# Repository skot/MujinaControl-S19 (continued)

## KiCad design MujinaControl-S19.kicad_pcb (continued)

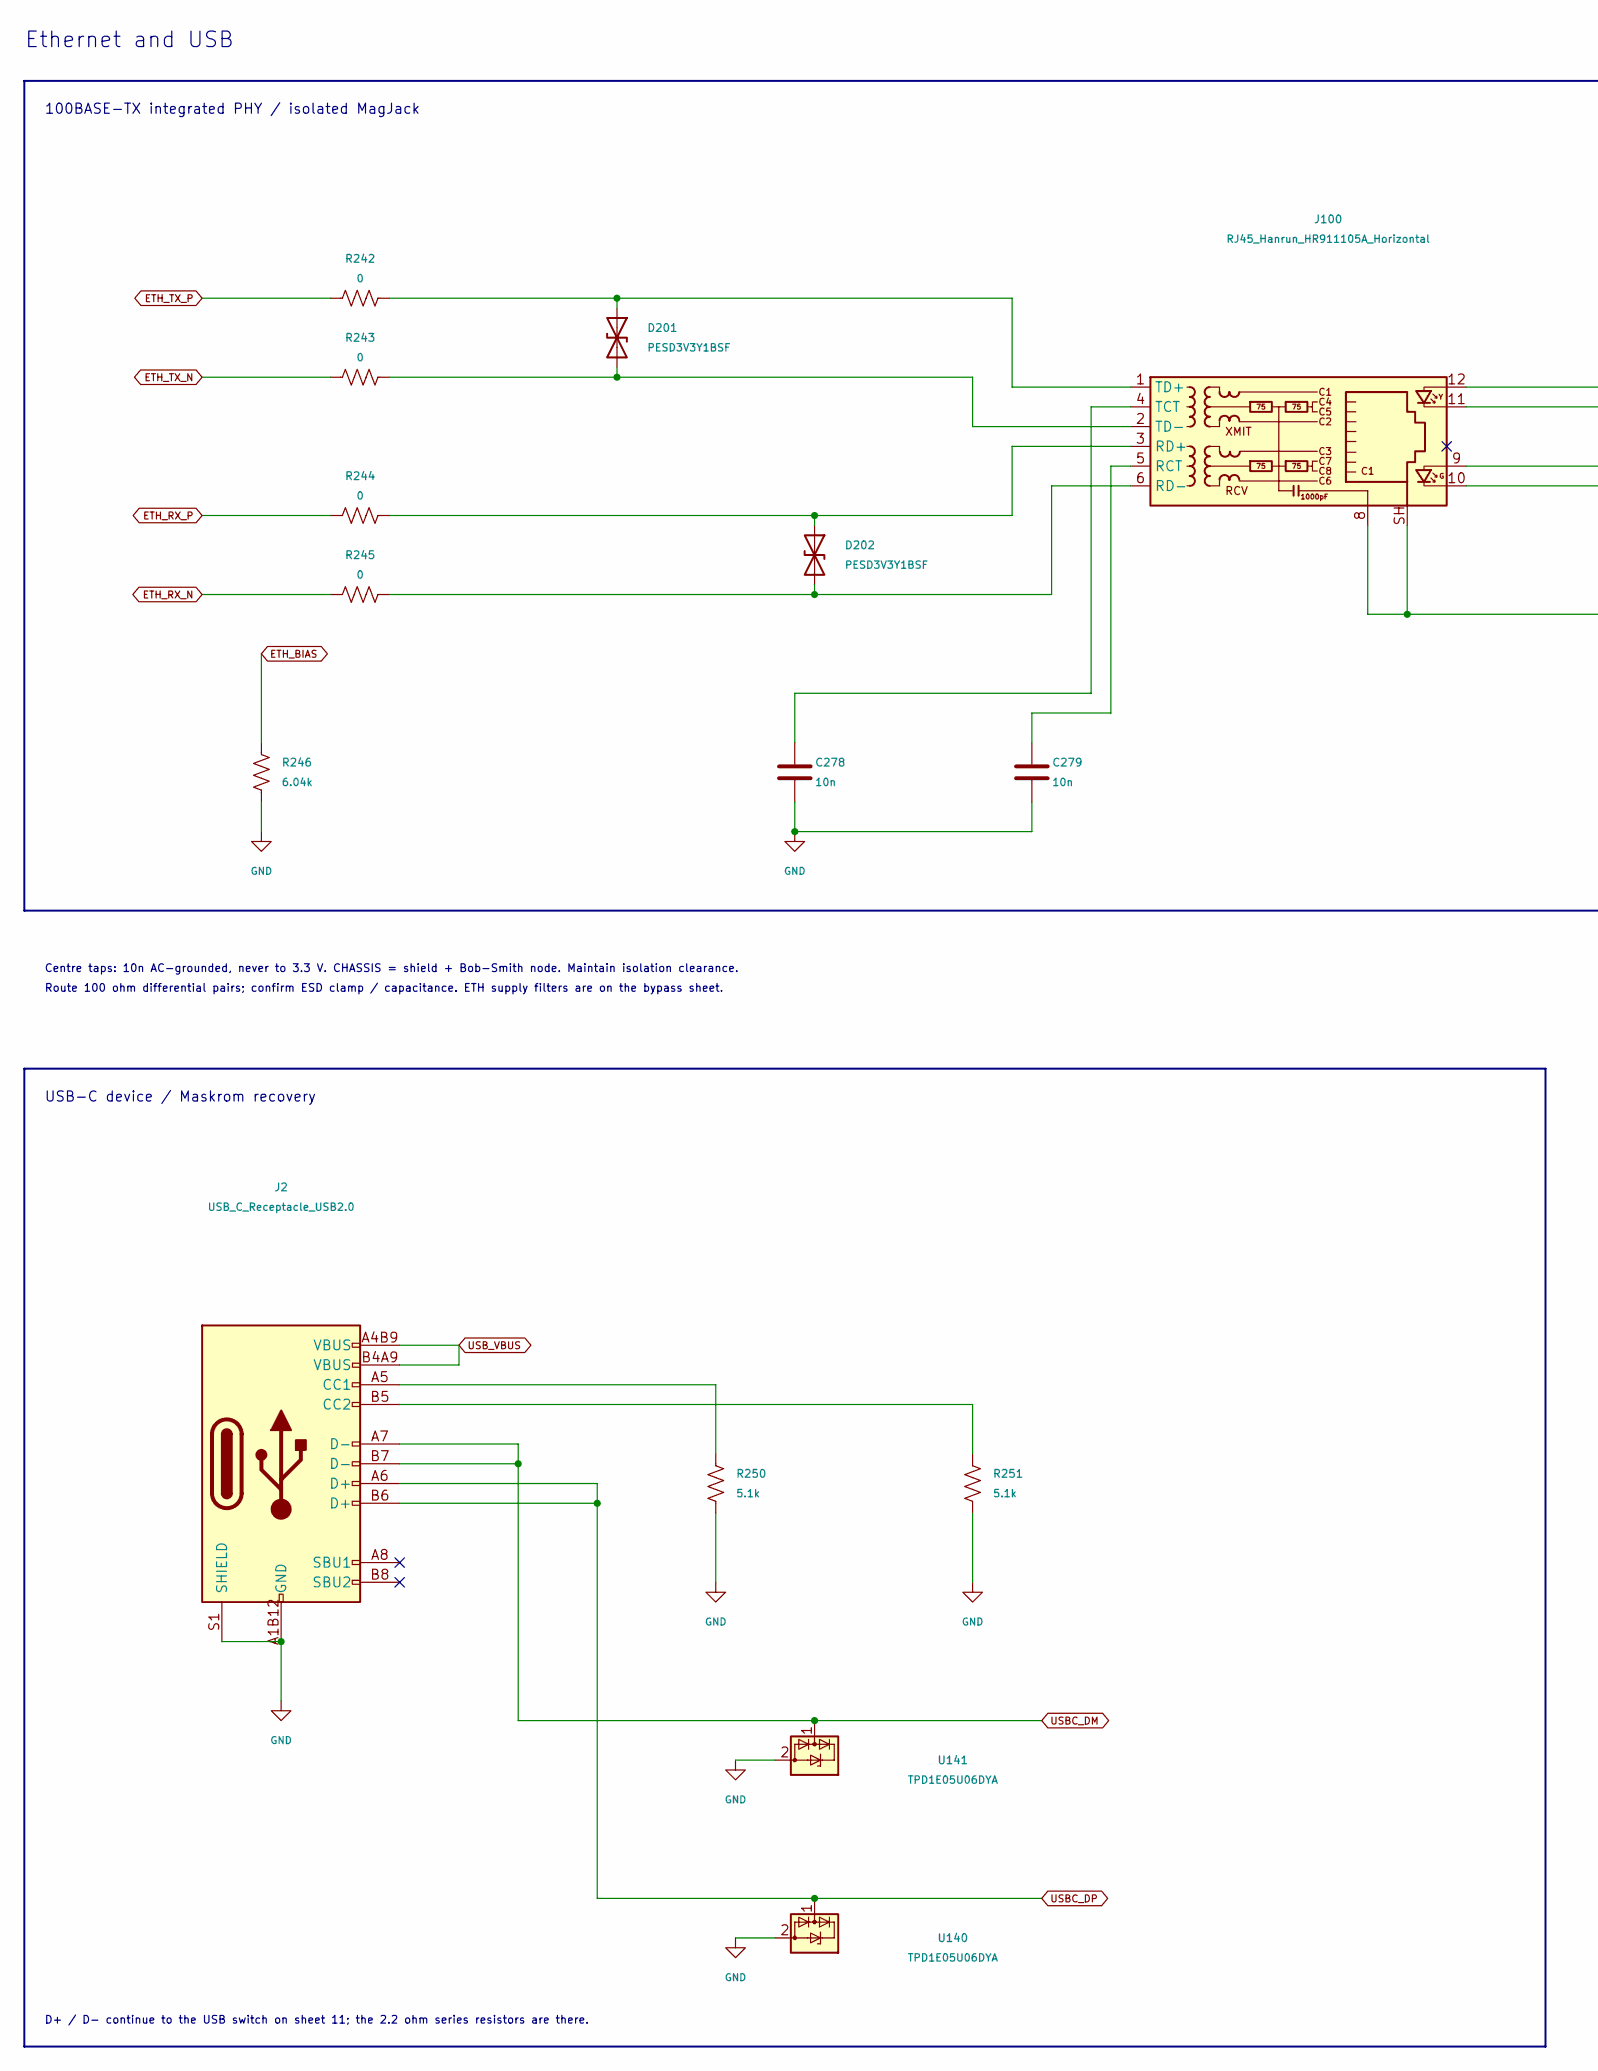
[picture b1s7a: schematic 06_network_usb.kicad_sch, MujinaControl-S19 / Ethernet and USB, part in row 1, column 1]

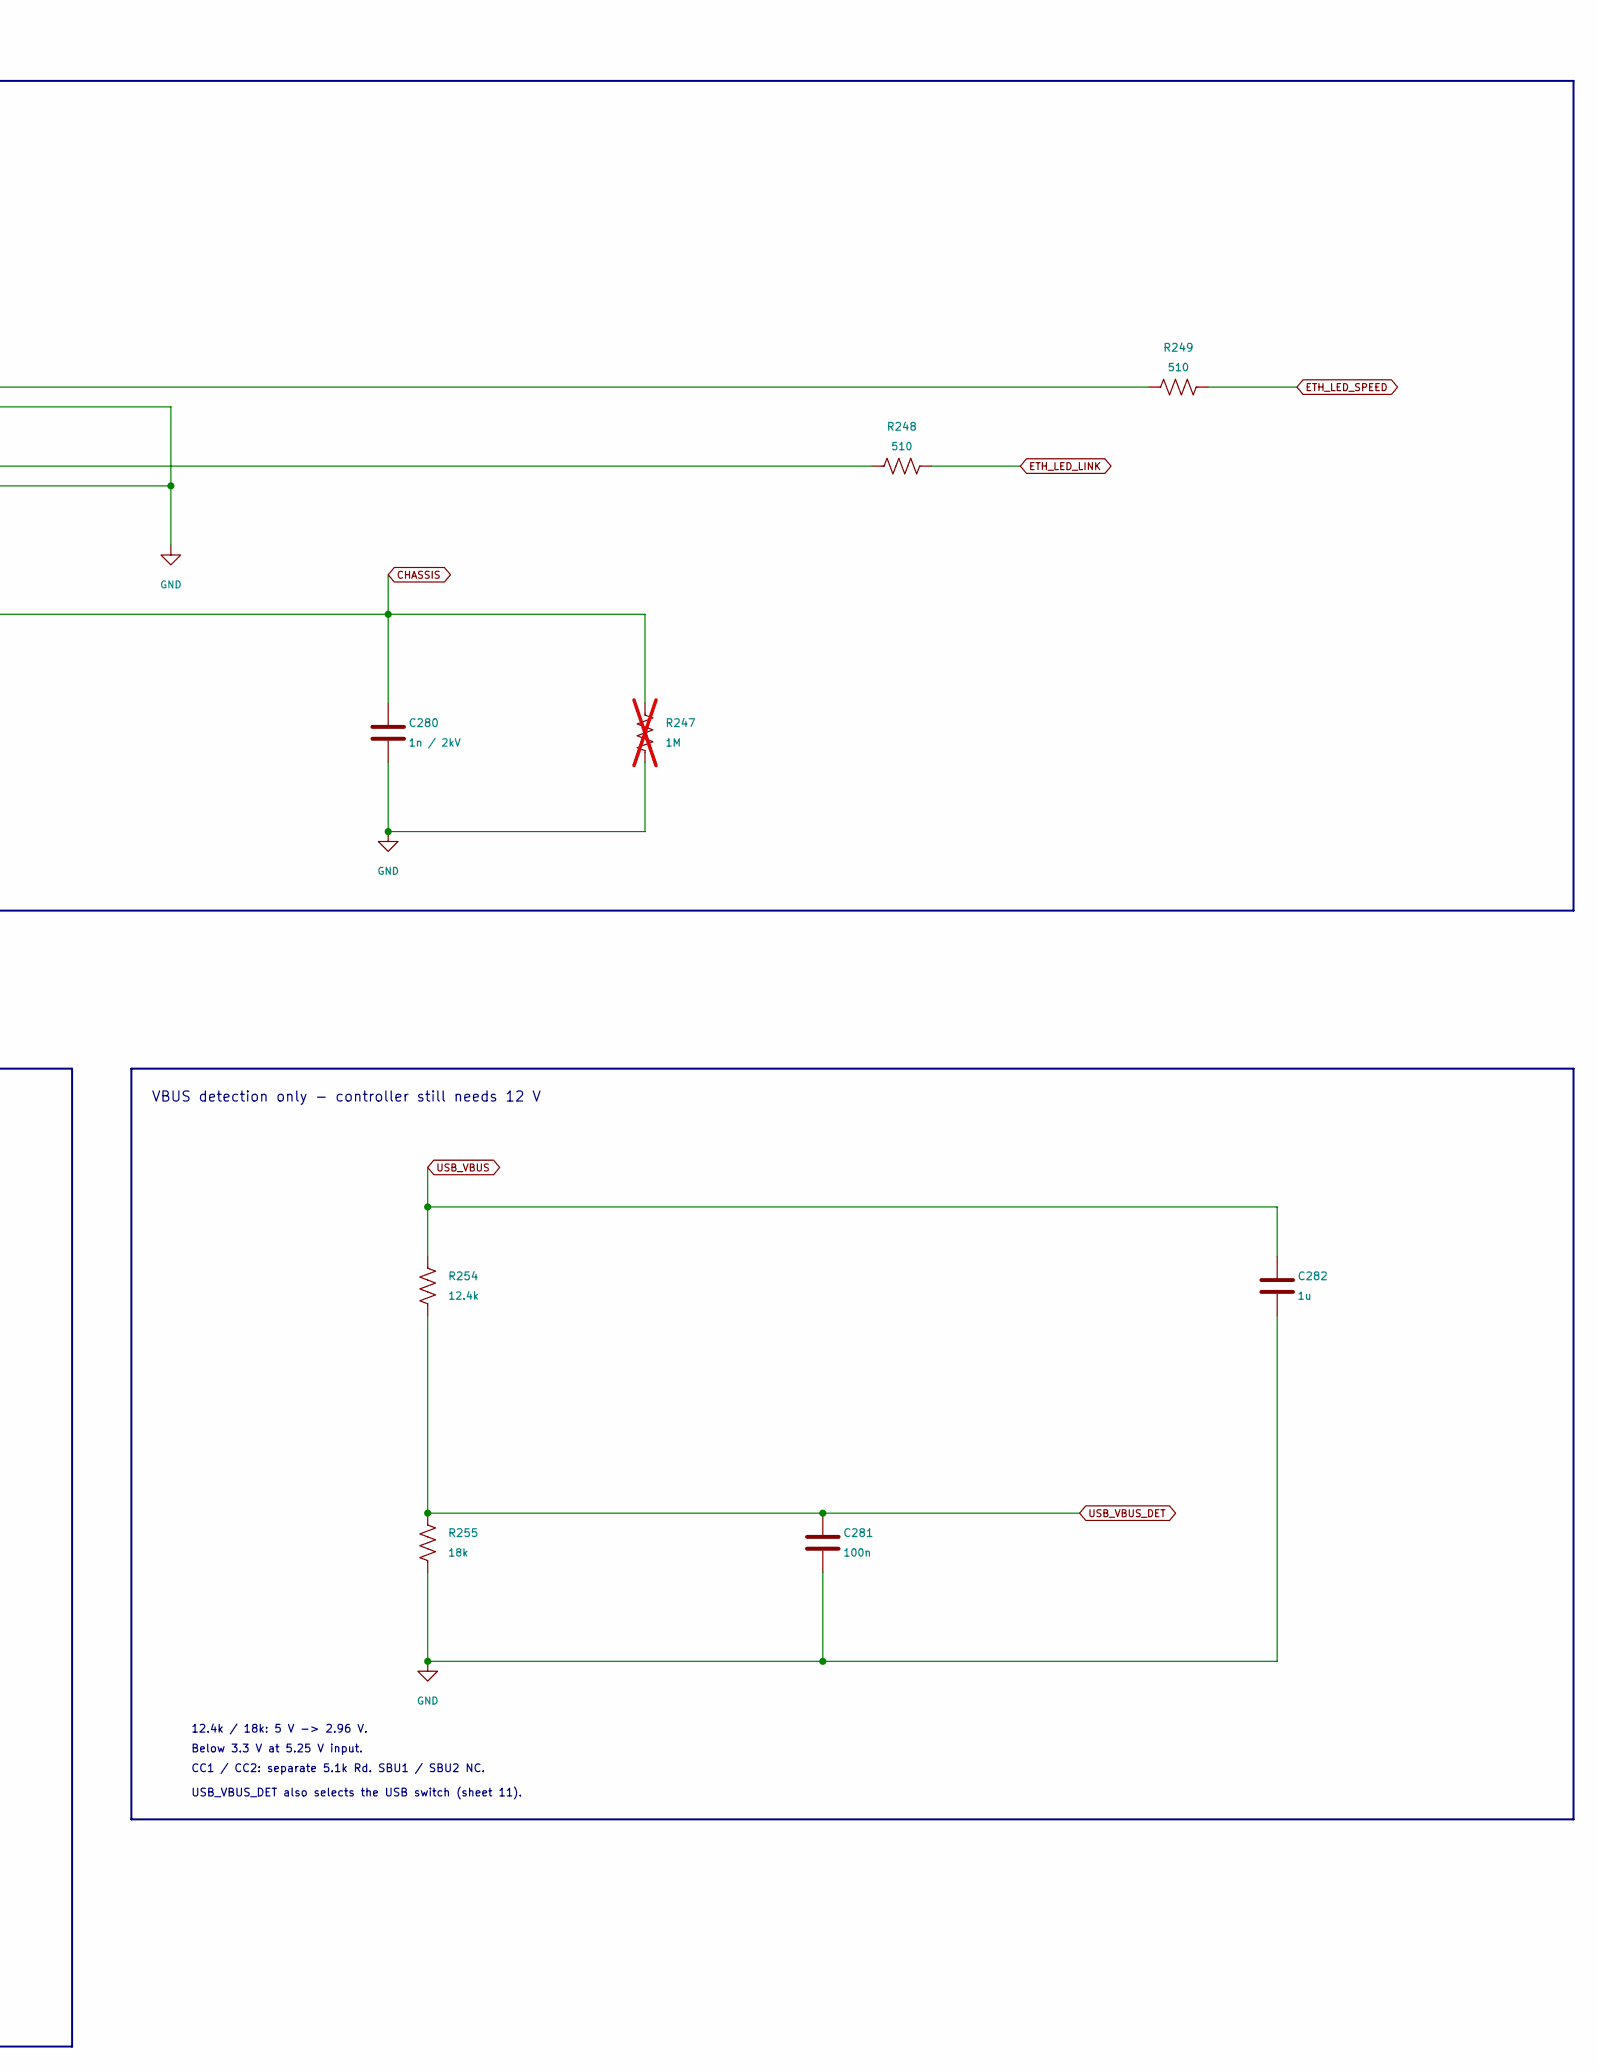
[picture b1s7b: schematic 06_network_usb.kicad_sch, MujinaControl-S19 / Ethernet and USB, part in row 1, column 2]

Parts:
C278, C279: 10n; C_0402_1005Metric; MPN CL05B103KB5NNNC; LCSC C15195
C280: 1n / 2kV; C_1808_4520Metric; MPN C1808C102KGRACTU; LCSC C2167485
C281: 100n; C_0402_1005Metric; MPN CL05B104KO5NNNC; LCSC C1525
C282: 1u; C_0402_1005Metric; MPN CL05A105KA5NQNC; LCSC C52923
D201, D202: PESD3V3Y1BSF; Nexperia_DSN0603-2_0.6x0.3mm_P0.4mm; MPN PESD3V3Y1BSFYL; LCSC C552535
J2: USB_C_Receptacle_USB2.0; USB_C_Receptacle_GCT_USB4105-xx-A_16P_TopMnt_Horizontal; MPN USB4105-GF-A; LCSC C3020560
J100: RJ45_Hanrun_HR911105A_Horizontal; MPN HR911105A; LCSC C12074
R242, R243, R244, R245: 0; R_0402_1005Metric; MPN 0402WGF0000TCE; LCSC C17168
R246: 6.04k; R_0402_1005Metric; MPN RC0402FR-076K04L; LCSC C97819
R247: 1M; R_0402_1005Metric; MPN 0402WGF1004TCE; LCSC C26083; not fitted
R248, R249: 510; R_0402_1005Metric; MPN 0402WGF5100TCE; LCSC C25123
R250, R251: 5.1k; R_0402_1005Metric; MPN 0402WGF5101TCE; LCSC C25905
R254: 12.4k; R_0402_1005Metric; MPN RC0402FR-0712K4L; LCSC C138060
R255: 18k; R_0402_1005Metric; MPN 0402WGF1802TCE; LCSC C25762
U140, U141: TPD1E05U06DYA; D_SOD-523; MPN TPD1E05U06DYA; LCSC C3702980

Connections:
CHASSIS: C280.1, J100.8, J100.SH, R247.1
ETH_BIAS: R246.1; also elsewhere on the board
ETH_LED_LINK: R248.1; also elsewhere on the board
ETH_LED_SPEED: R249.1; also elsewhere on the board
ETH_RX_N: R245.1; also elsewhere on the board
ETH_RX_P: R244.1; also elsewhere on the board
ETH_TX_N: R243.1; also elsewhere on the board
ETH_TX_P: R242.1; also elsewhere on the board
GND: C278.2, C279.2, C280.2, C281.2, C282.2, J2.A1B12 (GND), J2.B1A12 (GND), J2.S1 (SHIELD), J100.10, J100.11, R246.2, R247.2, R250.2, R251.2, R255.2, U140.2 (GND), U141.2 (GND); also elsewhere on the board
unnamed: D201.1 (A1), J100.1 (TD+), R242.2
unnamed: D201.2 (A2), J100.2 (TD-), R243.2
unnamed: D202.1 (A1), J100.3 (RD+), R244.2
unnamed: D202.2 (A2), J100.6 (RD-), R245.2
unnamed: J2.A5 (CC1), R250.1
unnamed: J2.B5 (CC2), R251.1
unnamed: J100.9, R248.2
unnamed: J100.12, R249.2
unnamed: C279.1, J100.5 (RCT)
unnamed: C278.1, J100.4 (TCT)
USBC_DM: J2.A7 (D-), J2.B7 (D-), U141.1 (I/O); also elsewhere on the board
USBC_DP: J2.A6 (D+), J2.B6 (D+), U140.1 (I/O); also elsewhere on the board
USB_VBUS: C282.1, J2.A4B9 (VBUS), J2.B4A9 (VBUS), R254.1
USB_VBUS_DET: C281.1, R254.2, R255.1; also elsewhere on the board

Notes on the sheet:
Ethernet and USB
100BASE-TX integrated PHY / isolated MagJack
USB_VBUS_DET also selects the USB switch (sheet 11).
12.4k / 18k: 5 V -> 2.96 V.
D+ / D- continue to the USB switch on sheet 11; the 2.2 ohm series resistors are there.
Centre taps: 10n AC-grounded, never to 3.3 V. CHASSIS = shield + Bob-Smith node. Maintain isolation clearance.
Route 100 ohm differential pairs; confirm ESD clamp / capacitance. ETH supply filters are on the bypass sheet.
Below 3.3 V at 5.25 V input.
CC1 / CC2: separate 5.1k Rd. SBU1 / SBU2 NC.
VBUS detection only - controller still needs 12 V
USB-C device / Maskrom recovery

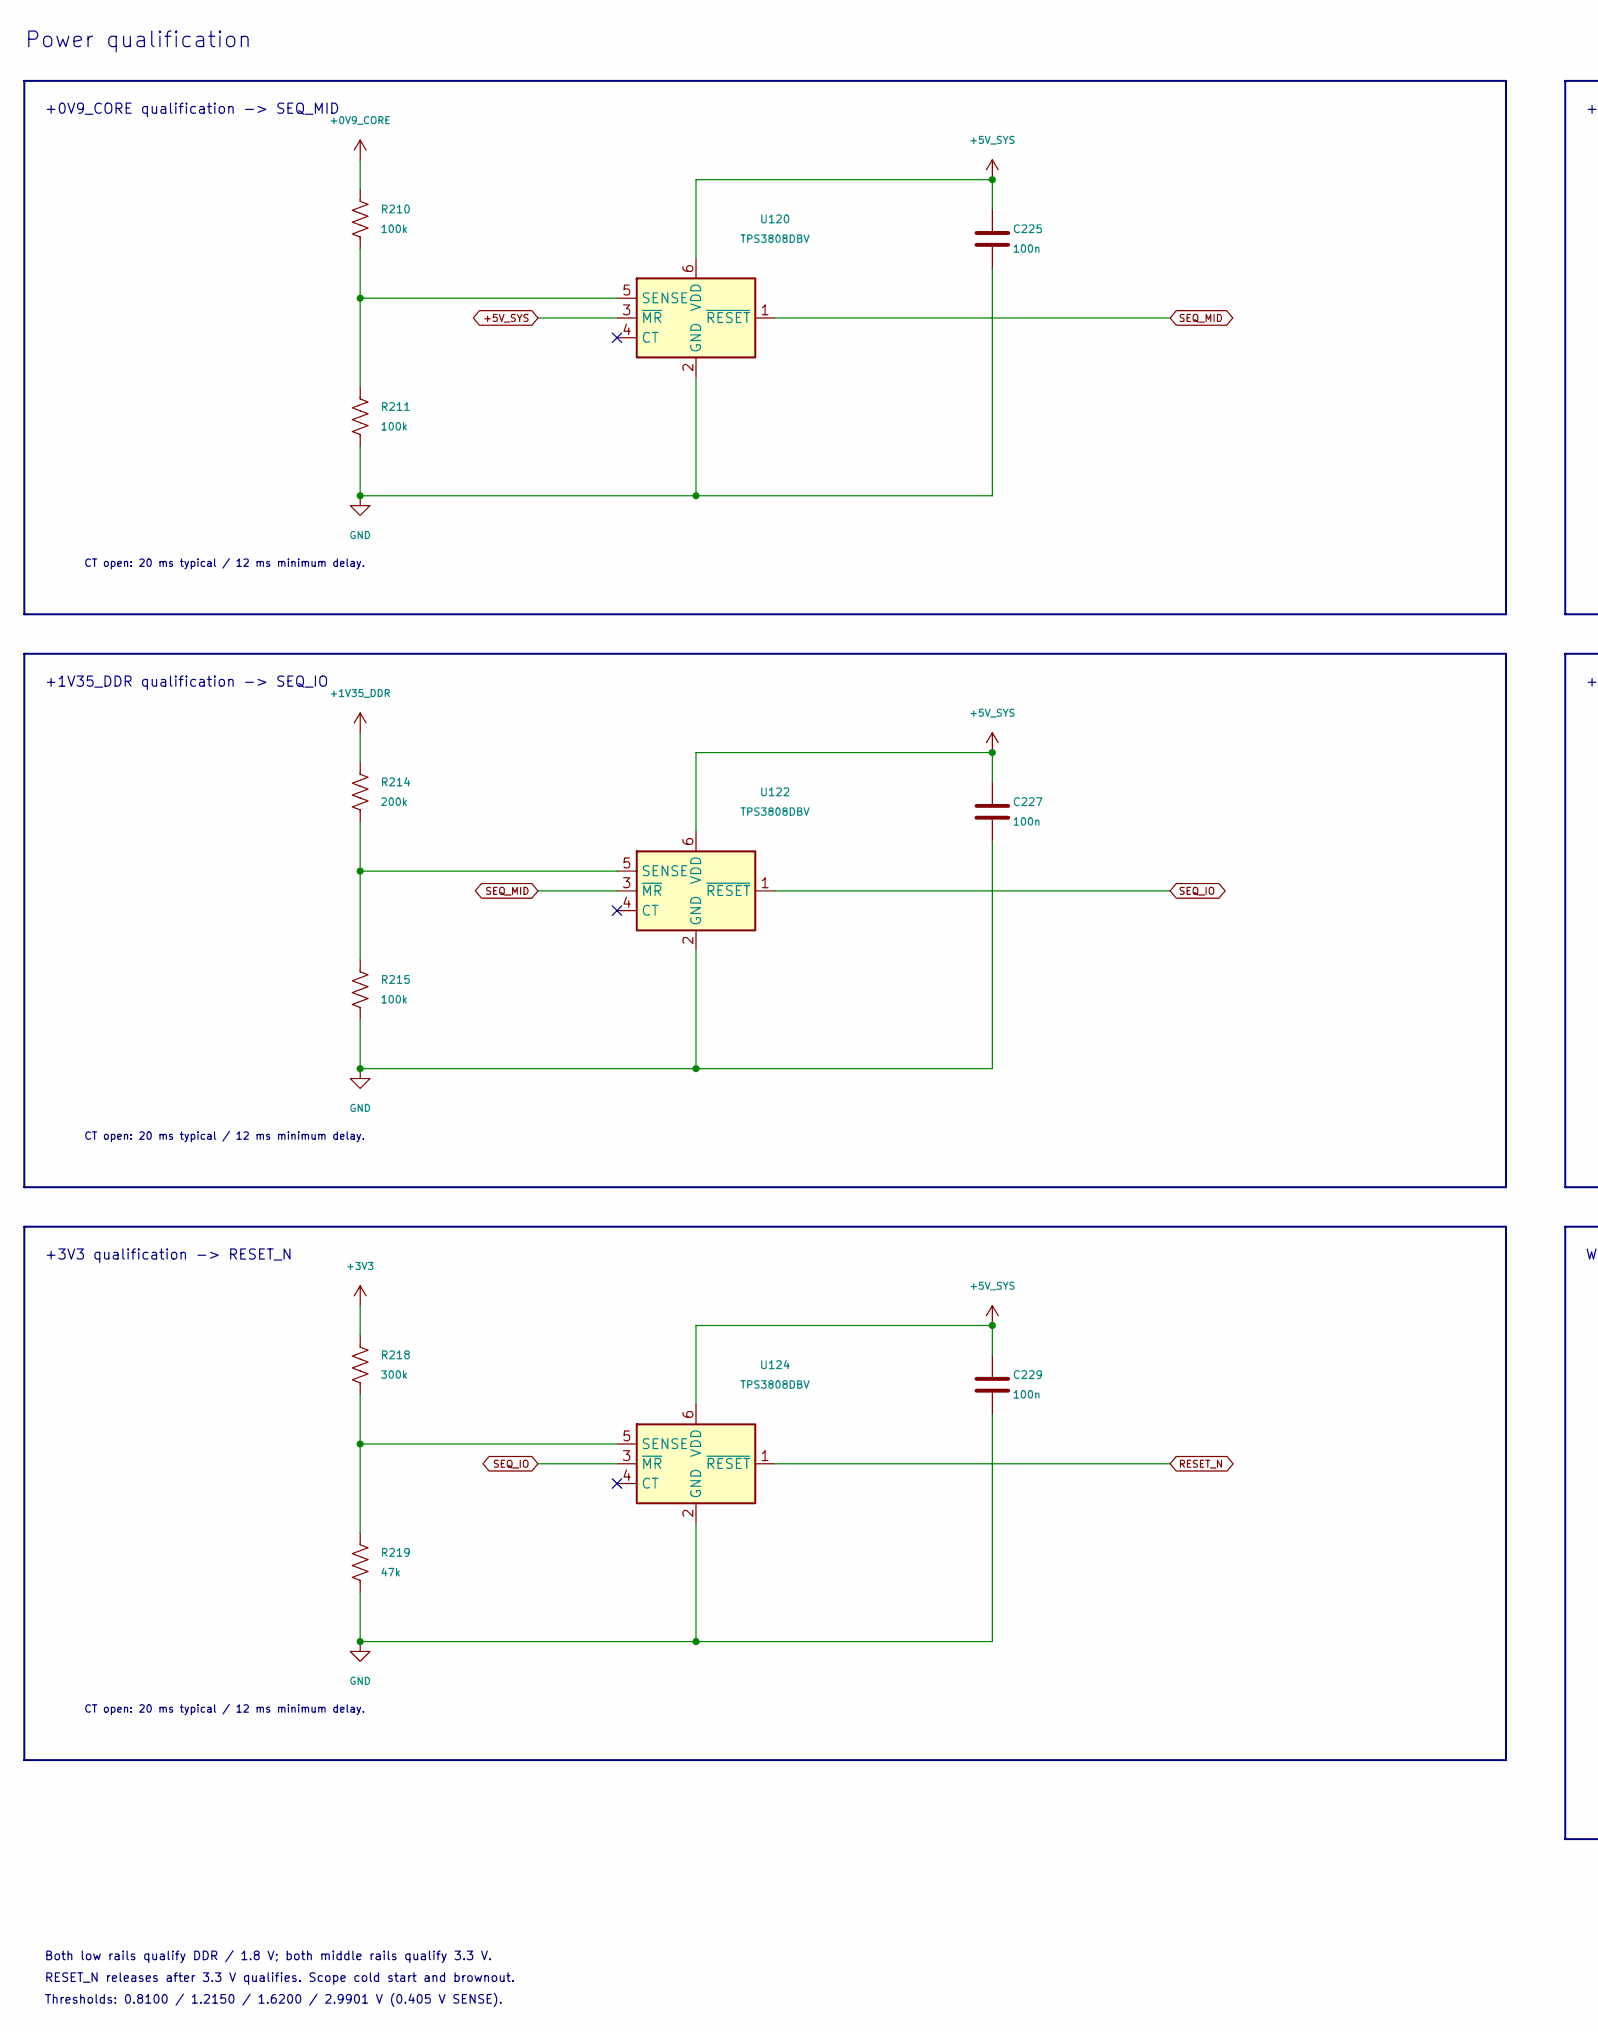
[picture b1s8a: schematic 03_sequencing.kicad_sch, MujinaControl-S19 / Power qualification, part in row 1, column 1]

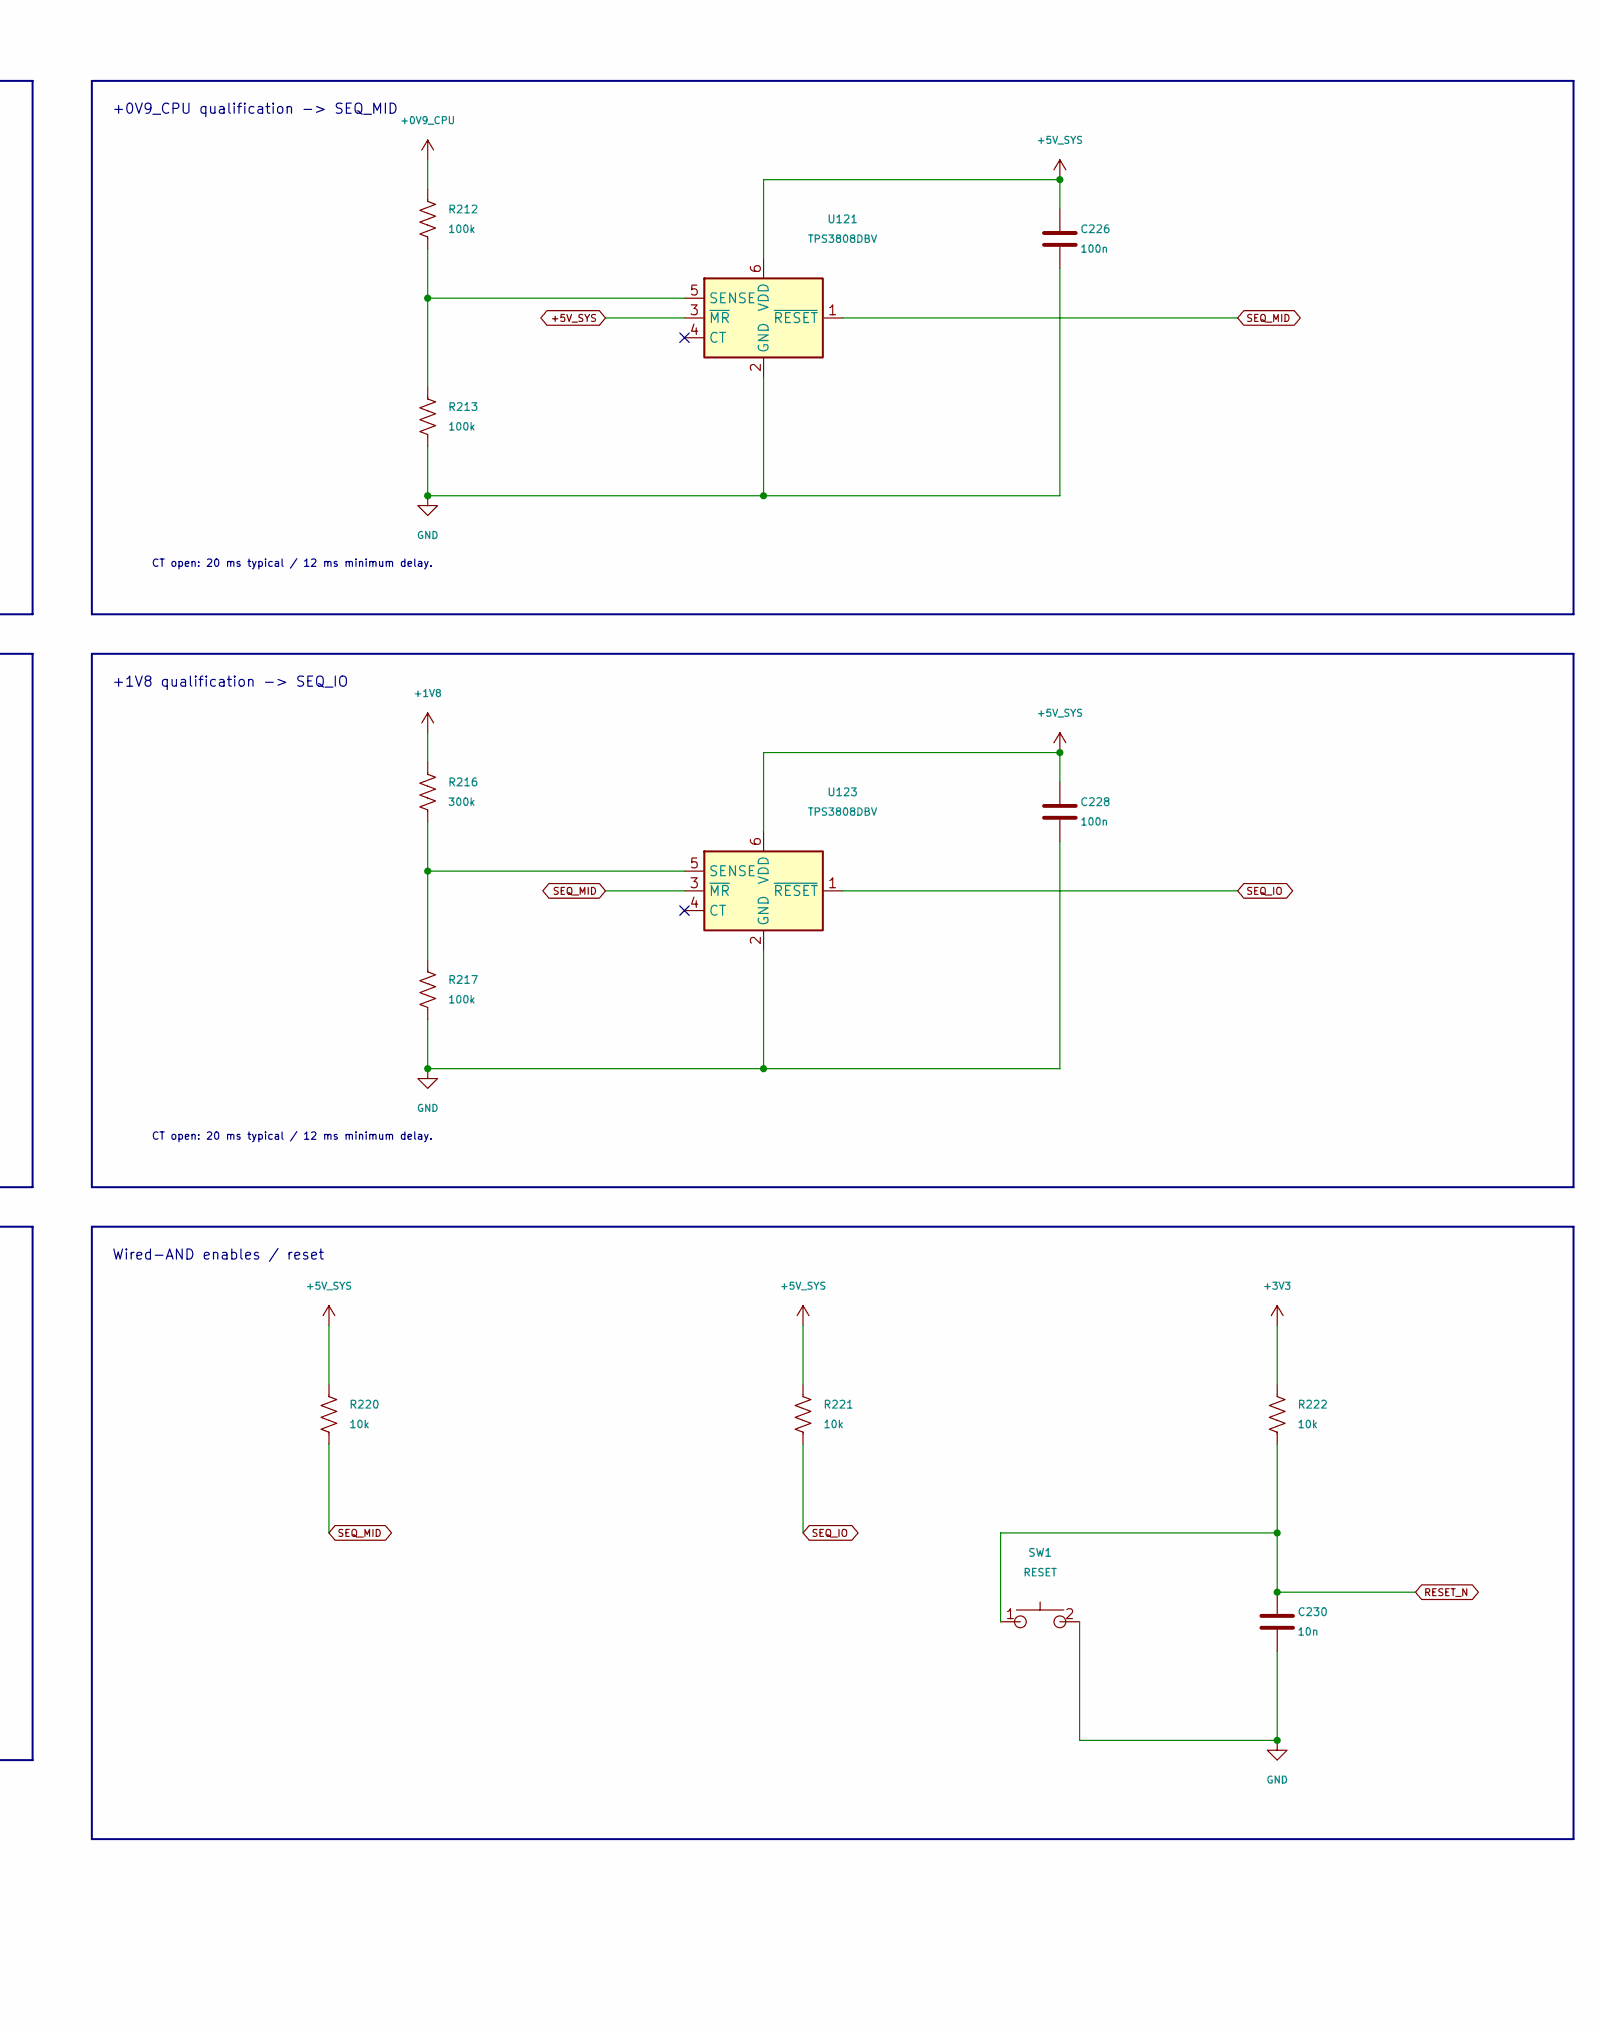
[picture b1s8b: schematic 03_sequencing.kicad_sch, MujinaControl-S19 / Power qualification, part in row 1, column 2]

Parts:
C225, C226, C227, C228, C229: 100n; C_0402_1005Metric; MPN CL05B104KO5NNNC; LCSC C1525
C230: 10n; C_0402_1005Metric; MPN CL05B103KB5NNNC; LCSC C15195
R210, R211, R212, R213, R215, R217: 100k; R_0402_1005Metric; MPN 0402WGF1003TCE; LCSC C25741
R214: 200k; R_0402_1005Metric; MPN 0402WGF2003TCE; LCSC C25764
R216, R218: 300k; R_0402_1005Metric; MPN 0402WGF3003TCE; LCSC C25774
R219: 47k; R_0402_1005Metric; MPN 0402WGF4702TCE; LCSC C25792
R220, R221, R222: 10k; R_0402_1005Metric; MPN 0402WGF1002TCE; LCSC C25744
SW1: RESET; SW-SMD_TC-S3601-3.5-260G-F0.6; MPN TC-S3601-3.5-260G-F0.6; LCSC C49101620
U120, U121, U122, U123, U124: TPS3808DBV; SOT-23-6; MPN TPS3808G01DBVR-TP; LCSC C42394092

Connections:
+0V9_CORE: R210.1; also elsewhere on the board
+0V9_CPU: R212.1; also elsewhere on the board
+1V8: R216.1; also elsewhere on the board
+1V35_DDR: R214.1; also elsewhere on the board
+3V3: R218.1, R222.1; also elsewhere on the board
+5V_SYS: C225.1, C226.1, C227.1, C228.1, C229.1, R220.1, R221.1, U120.3 (~MR), U120.6 (VDD), U121.3 (~MR), U121.6 (VDD), U122.6 (VDD), U123.6 (VDD), U124.6 (VDD); also elsewhere on the board
GND: C225.2, C226.2, C227.2, C228.2, C229.2, C230.2, R211.2, R213.2, R215.2, R217.2, R219.2, SW1.2, U120.2 (GND), U121.2 (GND), U122.2 (GND), U123.2 (GND), U124.2 (GND); also elsewhere on the board
unnamed: R210.2, R211.1, U120.5 (SENSE)
unnamed: R212.2, R213.1, U121.5 (SENSE)
unnamed: R214.2, R215.1, U122.5 (SENSE)
unnamed: R216.2, R217.1, U123.5 (SENSE)
unnamed: R218.2, R219.1, U124.5 (SENSE)
RESET_N: C230.1, R222.2, SW1.1, U124.1 (~RESET); also elsewhere on the board
SEQ_IO: R221.2, U122.1 (~RESET), U123.1 (~RESET), U124.3 (~MR); also elsewhere on the board
SEQ_MID: R220.2, U120.1 (~RESET), U121.1 (~RESET), U122.3 (~MR), U123.3 (~MR); also elsewhere on the board

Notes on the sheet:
Wired-AND enables / reset
+1V8 qualification -> SEQ_IO
+0V9_CPU qualification -> SEQ_MID
+1V35_DDR qualification -> SEQ_IO
Thresholds: 0.8100 / 1.2150 / 1.6200 / 2.9901 V (0.405 V SENSE).
+3V3 qualification -> RESET_N
+0V9_CORE qualification -> SEQ_MID
Both low rails qualify DDR / 1.8 V; both middle rails qualify 3.3 V.
RESET_N releases after 3.3 V qualifies. Scope cold start and brownout.
Power qualification
CT open: 20 ms typical / 12 ms minimum delay.

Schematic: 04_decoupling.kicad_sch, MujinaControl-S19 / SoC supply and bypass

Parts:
C231, C232, C233, C234, C235, C236, C237, C238, C239, C241, C243, C244, C245, C247, C248, C249, C250, C251, C252, C253, C255, C256, C257, C258, C262, C263, C265: 100n; C_0402_1005Metric; MPN CL05B104KO5NNNC; LCSC C1525
C240, C242, C246, C254, C259, C260: 10u; C_0805_2012Metric; MPN CL21A106KAYNNNE; LCSC C15850
C261, C264, C266, C267: 1u; C_0402_1005Metric; MPN CL05A105KA5NQNC; LCSC C52923
FB201, FB202: 120R @ 100MHz; L_0402_1005Metric; MPN BLM15AG121SN1D; LCSC C85812
H1, H2, H3, H4: MountingHole_Pad; MountingHole_3mm_Pad; MPN PCB_MOUNTING_HOLE; LCSC N/A
R223: 1; R_0402_1005Metric; MPN 0402WGF100KTCE; LCSC C25086
R224: 100; R_0402_1005Metric; MPN 0402WGF1000TCE; LCSC C25076
U100: RV1106G2; Rockchip_QFN-128-1EP_12.3x12.3mm_P0.35mm_EP7x7mm; MPN RV1106G2; LCSC C5272606

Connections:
+0V9_CORE: C231.1, C232.1, C233.1, C234.1, C235.1, C236.1, C237.1, C238.1, C239.1, C240.1, C260.1, U100.10 (DVDD_1), U100.51 (DVDD_2), U100.54 (DVDD_3), U100.55 (DVDD_4), U100.67 (PMU_DVDD0V9), U100.71 (OSC_PLL_DVDD), U100.82 (DVDD_5), U100.103 (DVDD_6), U100.116 (DVDD_7); also elsewhere on the board
+0V9_CPU: C241.1, C242.1, C261.1, U100.115 (CPU_DVDD); also elsewhere on the board
+1V8: C255.1, C256.1, C257.1, C258.1, C259.1, FB201.1, R223.1, U100.1 (MIPI_AVDD1V8), U100.31 (CODEC_AVDD1V8), U100.53 (DDR_PLL_AVDD1V8), U100.70 (OSC_AVDD1V8); also elsewhere on the board
+1V35_DDR: C243.1, C244.1, C245.1, C246.1, U100.49 (DDR_VDDQ_1), U100.50 (DDR_VDDQ_2), U100.56 (DDR_VDDQ_3); also elsewhere on the board
+3V3: C247.1, C248.1, C249.1, C250.1, C251.1, C252.1, C253.1, C254.1, FB202.1, R224.1, U100.13 (GPIO4_VCC), U100.28 (USB_AVDD3V3), U100.43 (GPIO3_VCC), U100.61 (PMU_VCC3V3), U100.81 (GPIO1_VCC3V3), U100.88 (GPIO6_VCC), U100.108 (GPIO5_VCC); also elsewhere on the board
ETH_1V8: C263.1, C264.1, FB201.2, U100.96 (OTP_AVDD1V8)
ETH_3V3: C265.1, C266.1, FB202.2, U100.101 (ETH_AVDD3V3)
GND: C231.2, C232.2, C233.2, C234.2, C235.2, C236.2, C237.2, C238.2, C239.2, C240.2, C241.2, C242.2, C243.2, C244.2, C245.2, C246.2, C247.2, C248.2, C249.2, C250.2, C251.2, C252.2, C253.2, C254.2, C255.2, C256.2, C257.2, C258.2, C259.2, C260.2, C261.2, C262.2, C263.2, C264.2, C265.2, C266.2, C267.2, H1.1 (1_1), H2.1 (1_1), H3.1 (1_1), H4.1 (1_1), U100.37 (GND), U100.57 (GND), U100.129 (GND_EP); also elsewhere on the board
RTC_3V3: C267.1, R224.2, U100.19 (RTC_AVDD3V3)
USB_1V8: C262.1, R223.2, U100.24 (SARADC_USB_AVDD1V8)

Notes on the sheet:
DDR3L: 1.35 V
CPU supply
Place each ceramic at its supply pin. Tie all ground pins and EP129
SoC supply and bypass
1.8 V analog / I/O
ETH_1V8 also supplies OTP / TSADC; place bead at pin 96.
to solid ground planes. RTC 100R / 1u is required by Rockchip.
U100 power distribution / exposed pad
Bulk / filtered analog rails
Core: one 100n per supply pin
Chassis mounting pads
3.3 V I/O

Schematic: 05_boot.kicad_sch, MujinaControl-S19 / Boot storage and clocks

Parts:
C268, C271: 100n; C_0402_1005Metric; MPN CL05B104KO5NNNC; LCSC C1525
C269, C277: 1u; C_0402_1005Metric; MPN CL05A105KA5NQNC; LCSC C52923
C270: 10u; C_0805_2012Metric; MPN CL21A106KAYNNNE; LCSC C15850
C272, C273, C274, C275: 18p; C_0402_1005Metric; MPN 0402CG180J500NT; LCSC C1549
C276: 1n; C_0402_1005Metric; MPN 0402B102K500NT; LCSC C1523
J16: UART2 DEBUG; PinHeader_1x03_P2.54mm_Vertical; MPN 61300311121; LCSC C2915006
J18: JTAG; PinHeader_1x05_P2.54mm_Vertical; MPN 61300511121; LCSC C6461551; not fitted
J101: Micro_SD_Card_Det2; microSD_HC_Hirose_DM3D-SF; MPN DM3D-SF; LCSC C719027
R225, R235, R236: 22; R_0402_1005Metric; MPN 0402WGF220JTCE; LCSC C25092
R226, R227, R228, R229, R230, R231, R232, R233, R234, R238, R240: 10k; R_0402_1005Metric; MPN 0402WGF1002TCE; LCSC C25744
R237: 1M; R_0402_1005Metric; MPN 0402WGF1004TCE; LCSC C26083; not fitted
R239: 100; R_0402_1005Metric; MPN 0402WGF1000TCE; LCSC C25076
R241: 240; R_0402_1005Metric; MPN RC0402FR-07240RL; LCSC C114755
SW2: BOOT; SW-SMD_TC-S3601-3.5-260G-F0.6; MPN TC-S3601-3.5-260G-F0.6; LCSC C49101620
U130: W25N02KVZEIR; WSON-8-1EP_8x6mm_P1.27mm_EP3.4x4.3mm; MPN W25N02KVZEIR; LCSC C3010298
Y100: 24MHz / CL12pF; Crystal_SMD_3225-4Pin_3.2x2.5mm; MPN X322524MOB4SI; LCSC C70590
Y101: 32.768kHz / CL12.5pF; Crystal_SMD_3215-2Pin_3.2x1.5mm; MPN Q13FC13500004; LCSC C32346

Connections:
+1V8: R238.1; also elsewhere on the board
+3V3: C268.1, C269.1, C270.1, C271.1, J18.1, J101.4 (VDD), R226.1, R227.1, R228.1, R229.1, R230.1, R231.1, R232.1, R233.1, R234.1, R240.1, U130.8 (VCC); also elsewhere on the board
BOOT_ADC: C276.1, R238.2, R239.1; also elsewhere on the board
CODEC_VCM: C277.1; also elsewhere on the board
DEBUG_RX: J16.3, R240.2; also elsewhere on the board
DEBUG_TX: J16.1; also elsewhere on the board
DRAM_ZQ: R241.1; also elsewhere on the board
FSPI_CLK: R225.2, U130.6 (SCLK)
FSPI_CLK_SOC: R225.1; also elsewhere on the board
FSPI_CS_N: R226.2, U130.1 (~CS); also elsewhere on the board
FSPI_D0: U130.5 (SI/IO0); also elsewhere on the board
FSPI_D1: U130.2 (SO/IO1); also elsewhere on the board
FSPI_D2: R227.2, U130.3 (~WP/IO2); also elsewhere on the board
FSPI_D3: R228.2, U130.7 (~HOLD/~RESET/IO3); also elsewhere on the board
GND: C268.2, C269.2, C270.2, C271.2, C272.2, C273.2, C274.2, C275.2, C276.2, C277.2, J16.2, J18.5, J101.6 (VSS), J101.10 (DET_A), J101.SH (SHIELD), R241.2, SW2.2, U130.4 (VSS), U130.9 (PAD), Y100.2 (G), Y100.4 (G); also elsewhere on the board
unnamed: C272.1, R236.2, Y100.1
unnamed: R239.2, SW2.1
OSC_XIN: C273.1, R237.2, Y100.3; also elsewhere on the board
OSC_XOUT: R236.1, R237.1; also elsewhere on the board
RESET_N: J18.4; also elsewhere on the board
RTC_XIN: C274.1, Y101.1; also elsewhere on the board
RTC_XOUT: C275.1, Y101.2; also elsewhere on the board
SD_CLK: J101.5 (CLK), R235.2
SD_CLK_SOC: R235.1; also elsewhere on the board
SD_CMD: J101.3 (CMD), R229.2; also elsewhere on the board
SD_D0: J101.7 (DAT0), R230.2; also elsewhere on the board
SD_D1: J101.8 (DAT1), R231.2; also elsewhere on the board
SD_D2: J18.3, J101.1 (DAT2), R232.2; also elsewhere on the board
SD_D3: J18.2, J101.2 (DAT3/CD), R233.2; also elsewhere on the board
SD_DET_N: J101.9 (DET_B), R234.2; also elsewhere on the board

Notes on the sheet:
18p crystal loads assume ~3p parasitic: measure startup and frequency.
Main oscillator / RTC crystal
Boot storage and clocks
BOOT key / UART debug / JTAG header / bias
J16: 1 = SoC TX; 2 = GND; 3 = SoC RX. 3.3 V only.
microSD - development / alternate boot
J18 (not fitted): 1 = 3.3 V reference; 2 = TMS (SD_D3); 3 = TCK (SD_D2); 4 = RESET_N; 5 = GND.
256 MB SPI NAND - normal boot
JTAG is an alternate function of the SD_D2 / SD_D3 pins (JTAG_CPU_TCK_M0 / TMS_M0): use it with no microSD card inserted.
SPI NAND has priority over SD. Hold BOOT during reset for USB recovery.
CPU JTAG, 2-wire - not fitted

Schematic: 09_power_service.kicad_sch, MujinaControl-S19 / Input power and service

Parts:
C283, C303, C304, C305: 100n; C_0402_1005Metric; MPN CL05B104KO5NNNC; LCSC C1525
C284, C285: 10u / 50V; C_1210_3225Metric; MPN CL32B106KBJNNNE; LCSC C138687
C286, C302: 100n / 50V; C_0402_1005Metric; MPN CL05B104KB54PNC; LCSC C307331
C287, C288: 22u / 25V; C_0805_2012Metric; MPN CL21A226MAQNNNE; LCSC C45783
C301: 33n / 50V; C_0603_1608Metric; MPN CL10B333KB8NNNC; LCSC C21117
D2: BZX84C12; SOT-23-3_L2.9-W1.6-P1.90-LS2.8-BR; MPN BZX84C12; LCSC C19077471
D220: SMBJ15A; D_SMB; MPN SMBJ15A; LCSC C19077569
J1: 0455580003; CONN-TH_50362462; MPN 50362462; LCSC C492365
J10: PSU Comm; CONN-TH_6P-P2.00_PHD-2X3A; MPN HC-PHD-2*3A; LCSC C2845614
J15: ACC 2x20 / 0.1 in; PinHeader_2x20_P2.54mm_Vertical; MPN PZ2.54-2*20; LCSC C5224014; not fitted
L210: 1.5u; IND-SMD_L2.0-W1.6; MPN FTC201612S1R5MBCA; LCSC C5832350
Q1: NTTFS008P03P8Z; onsemi_WDFN-8_3.3x3.3mm_P0.65mm_CASE483AW; MPN NTTFS008P03P8Z; LCSC C894097
R270, R279: 10k; R_0402_1005Metric; MPN 0402WGF1002TCE; LCSC C25744
R271: 100k; R_0402_1005Metric; MPN 0402WGF1003TCE; LCSC C25741
R272, R273: 4.7k; R_0402_1005Metric; MPN 0402WGF4701TCE; LCSC C25900; not fitted
R282, R284: 27k; R_0402_1005Metric; MPN 0402WGF2702TCE; LCSC C25771
R283, R285: 5.1k; R_0402_1005Metric; MPN 0402WGF5101TCE; LCSC C25905
R286, R287: 4.7k; R_0402_1005Metric; MPN 0402WGF4701TCE; LCSC C25900
TP29, TP30: TestPoint; TestPoint_Pad_D1.0mm; MPN PCB_TESTPOINT; LCSC N/A
U115: TPS62933DRLR; SOT-583-8_L2.1-W1.2-P0.50-LS1.6-BR; MPN TPS62933DRLR; LCSC C3200405

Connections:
+1V8: C305.1, J15.26; also elsewhere on the board
+3V3: C304.1, J15.3, J15.4, R272.1, R273.1, R286.1, R287.1; also elsewhere on the board
+5V_SYS: C287.1, C288.1, C303.1, J15.1, J15.2, L210.2, R282.1; also elsewhere on the board
+12V_FAN: C283.1, C284.1, C285.1, C302.1, D2.3 (K), D220.1 (K), Q1.1 (S), Q1.2 (S), Q1.3 (S), R284.1, U115.3 (VIN); also elsewhere on the board
+12V_IN: J1.1, J1.2, J1.3, Q1.5 (D), Q1.6 (D), Q1.7 (D), Q1.8 (D)
ACC1V8_GPIO3_C4: J15.27; also elsewhere on the board
ACC1V8_GPIO3_C5: J15.28; also elsewhere on the board
ACC1V8_GPIO3_C6: J15.29; also elsewhere on the board
ACC1V8_GPIO3_C7: J15.33; also elsewhere on the board
ACC1V8_GPIO3_D0: J15.34; also elsewhere on the board
ACC1V8_GPIO3_D1: J15.35; also elsewhere on the board
ACC1V8_GPIO3_D2: J15.36; also elsewhere on the board
ACC1V8_GPIO3_D3: J15.30; also elsewhere on the board
ACC_GPIO0_A0: J15.10; also elsewhere on the board
ACC_GPIO0_A1: J15.9; also elsewhere on the board
ACC_GPIO0_A2: J15.15; also elsewhere on the board
ACC_GPIO0_A4: J15.16; also elsewhere on the board
ACC_GPIO4_A5: J15.12; also elsewhere on the board
ACC_GPIO4_A7: J15.11; also elsewhere on the board
ACC_I2C4_SCL: J15.5, R286.2; also elsewhere on the board
ACC_I2C4_SDA: J15.6, R287.2; also elsewhere on the board
GND: C283.2, C284.2, C285.2, C287.2, C288.2, C301.2, C302.2, C303.2, C304.2, C305.2, D220.2 (A), J1.4, J1.5, J1.6, J10.2, J15.7, J15.8, J15.13, J15.14, J15.19, J15.20, J15.23, J15.24, J15.25, J15.31, J15.32, J15.37, J15.38, J15.39, J15.40, R270.2, R271.2, R279.2, R283.2, R285.2, U115.4 (GND); also elsewhere on the board
unnamed: D2.1 (A), Q1.4 (G), R270.1
unnamed: C286.1, U115.6 (BST)
unnamed: R284.2, R285.1, U115.2 (EN)
unnamed: R282.2, R283.1, U115.8 (FB)
unnamed: R279.1, U115.1 (RT)
unnamed: C301.1, U115.7 (SS)
unnamed: C286.2, L210.1, U115.5 (SW)
PSU_AUX1: J10.1, TP29.1 (1_1)
PSU_AUX4: J10.4, TP30.1 (1_1)
PSU_EN: J10.5, R271.1; also elsewhere on the board
PSU_SCL: J10.6, R273.2; also elsewhere on the board
PSU_SDA: J10.3, R272.2; also elsewhere on the board

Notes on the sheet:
Controller branch / 5 V preregulator
17 / 18 : NC
3.8 mOhm max at VGS=-10 V; estimated hot loss ~1.1 W at 14 A.
27 / 28 : GPIO3_C4 / C5 : GPIO
1.8 V pins
9 / 10 : GPIO0_A1 / A0 : UART0 TX / RX (M0)
J1 retains the six-pin bitcrane power connector. Q1 protects both fan and controller supplies from reversed input. No onboard fuse: input fault disconnection relies on upstream protection.
No series, ESD or current-limit parts: no hot-plugging, keep loads small.
Bonanza 10k RT: 1.98 MHz; 33n SS: 4.8 ms.
I2C4 (5/6) has 4.7k pull-ups; other connected signals go to the SoC.
3.3 V
Input power and service
J15 is not fitted at assembly: solder a 2x20 header if it is needed.
Dedicated drain heat spreaders; qualify Tj <=125 C at 40 C ambient.
29 / 30 : GPIO3_C6 / D3 : PWM7 / PWM1 (M2)
J15: 2x20 0.1 in accessory header. Not Raspberry Pi pin-compatible.
33 / 34 : GPIO3_C7 / D0 : UART5 TX / RX (M2), or I2C4 SCL / SDA (M2)
Qualify transient, thermal and overload behavior.
Q1 design target: 14 A = four 3 A fans + 2 A controller allowance.
PWM1 reaches pins 16 / 30; use one of them.
PSU communication / enable defaults low
3.3 V pins
12 V input / reverse-polarity protection / fan supply
Reverse-polarity protection retained; no inrush or current limiting.
5 / 6 : GPIO2_A1 / A0 : I2C4 SCL / SDA (M0)
17 / 18 / 21 / 22 : NC; CPU GPIOs used for USB-A and HB power
J15 notes
Signals 5-16: 3.3 V; 17/18/21/22: NC. Signals 27-36: 1.8 V ONLY.
Accessory header J15 / spare SoC I/O
+1V8 (pin 26) is a level-shifter reference only, not a supply.
11 / 12 : GPIO4_A7 / A5 : I2C2 SCL / SDA (M1), SPI1 CLK / CS0
27k / 5.1k EN divider: starts near 7.6 V input.
15 / 16 : GPIO0_A2 / A4 : PWM3 / PWM1 (M0)
1.8 V ONLY
35 / 36 : GPIO3_D1 / D2 : UART5 RTS / CTS (M2), or I2C3 SCL / SDA (M2)
Confirm PSU enable polarity and cable-side pull-ups before fitting R272/R273. Hashboard bias is on sheet 8.
5.035 V / 2 A system budget; fan current bypasses U115.
No direct 12 V connection to EN (5.5 V limit).
